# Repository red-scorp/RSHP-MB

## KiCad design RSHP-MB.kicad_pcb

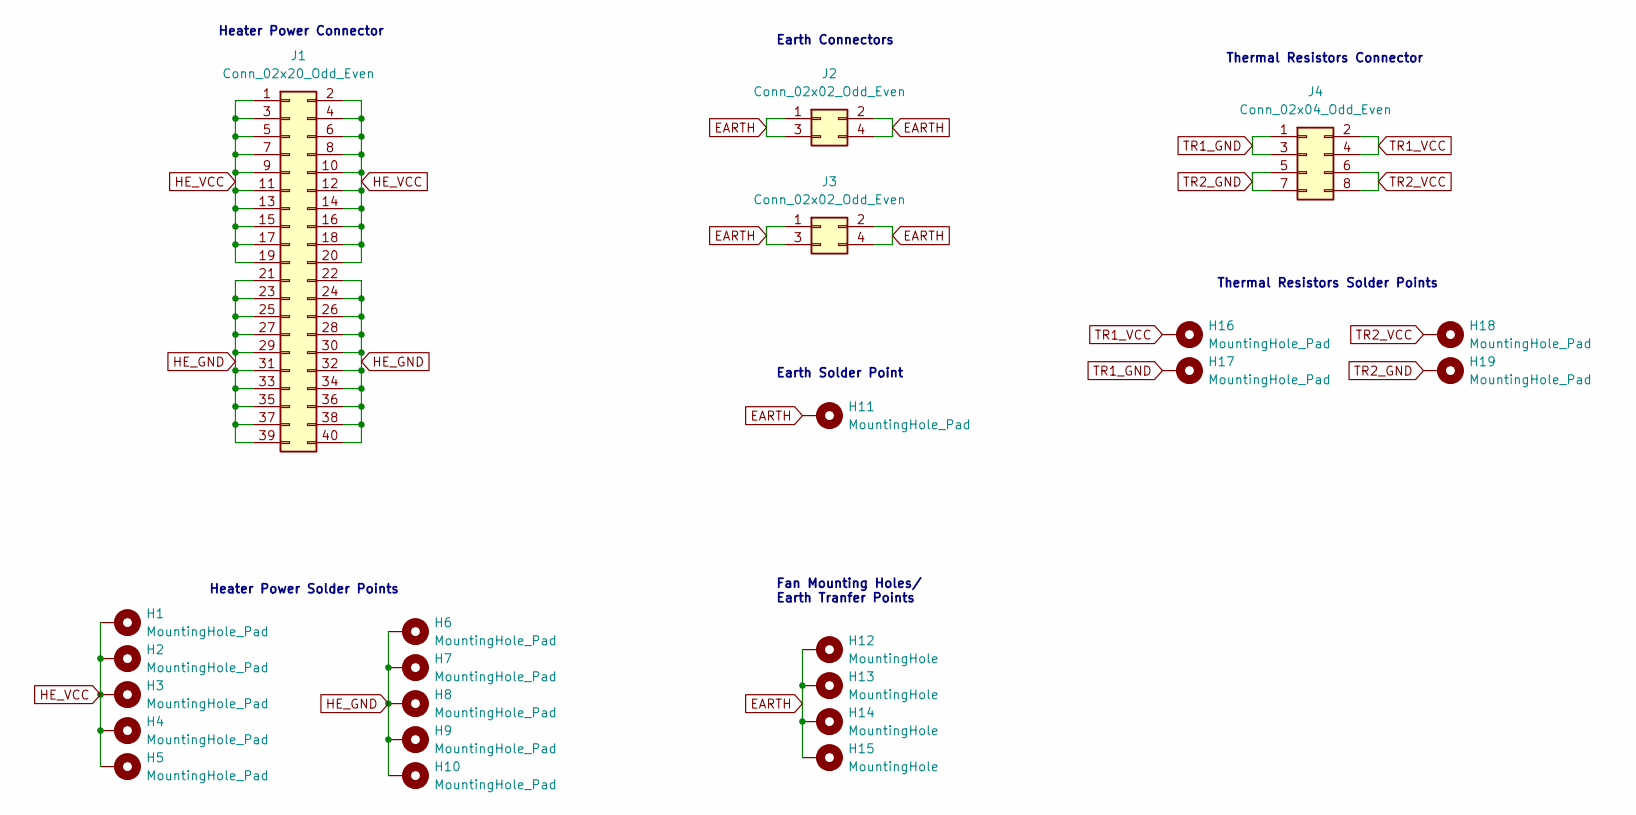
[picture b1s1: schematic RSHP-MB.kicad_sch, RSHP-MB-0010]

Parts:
H1, H2, H3, H4, H5, H6, H7, H8, H9, H10, H11, H16, H17, H18, H19: MountingHole_Pad; MountingHole_2.2mm_M2_Pad
H12, H13, H14, H15: MountingHole; MountingHole_4.3mm_M4_Pad
J1: Conn_02x20_Odd_Even; PinHeader_2x20_P2.54mm_Vertical
J2, J3: Conn_02x02_Odd_Even; PinHeader_2x02_P2.54mm_Vertical
J4: Conn_02x04_Odd_Even; PinHeader_2x04_P2.54mm_Vertical

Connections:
EARTH: H11.1, H12.1, H13.1, H14.1, H15.1, J2.1, J2.2, J2.3, J2.4, J3.1, J3.2, J3.3, J3.4
HE_GND: H6.1, H7.1, H8.1, H9.1, H10.1, J1.21, J1.22, J1.23, J1.24, J1.25, J1.26, J1.27, J1.28, J1.29, J1.30, J1.31, J1.32, J1.33, J1.34, J1.35, J1.36, J1.37, J1.38, J1.39, J1.40
HE_VCC: H1.1, H2.1, H3.1, H4.1, H5.1, J1.1, J1.2, J1.3, J1.4, J1.5, J1.6, J1.7, J1.8, J1.9, J1.10, J1.11, J1.12, J1.13, J1.14, J1.15, J1.16, J1.17, J1.18, J1.19, J1.20
TR1_GND: H17.1, J4.1, J4.3
TR1_VCC: H16.1, J4.2, J4.4
TR2_GND: H19.1, J4.5, J4.7
TR2_VCC: H18.1, J4.6, J4.8

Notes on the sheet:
Fan Mounting Holes/ Earth Tranfer Points
Heater Power Connector
Earth Connectors
Heater Power Solder Points
Earth Solder Point
Thermal Resistors Connector
Thermal Resistors Solder Points

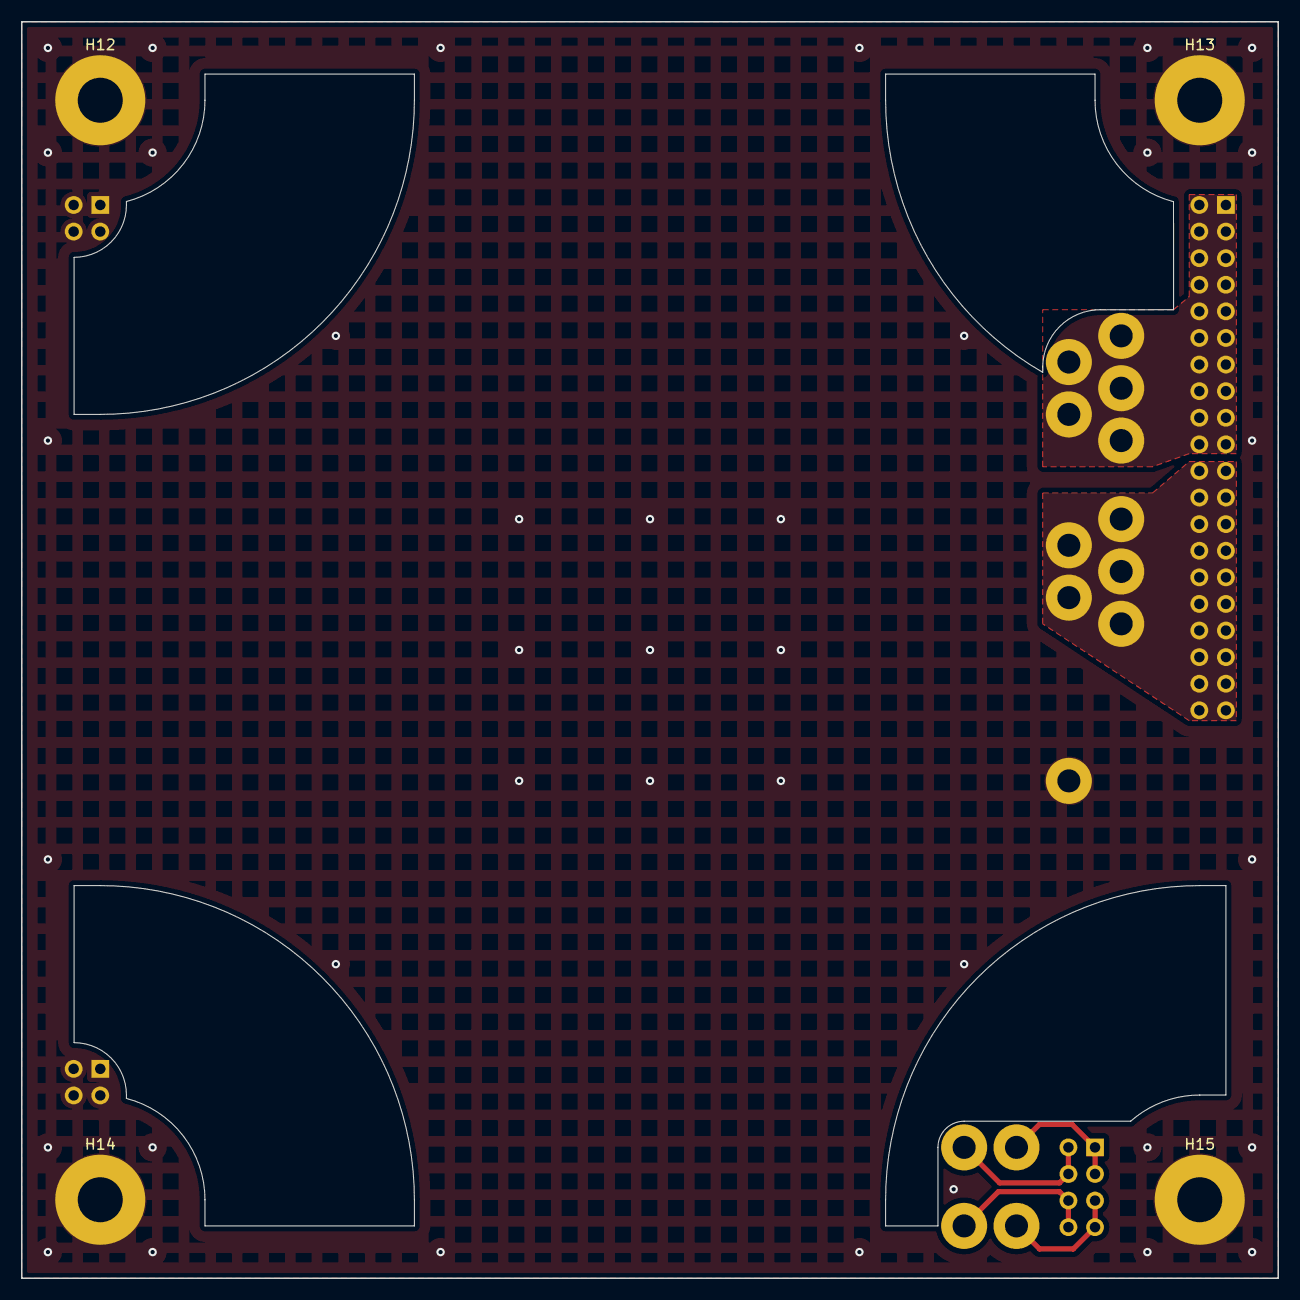
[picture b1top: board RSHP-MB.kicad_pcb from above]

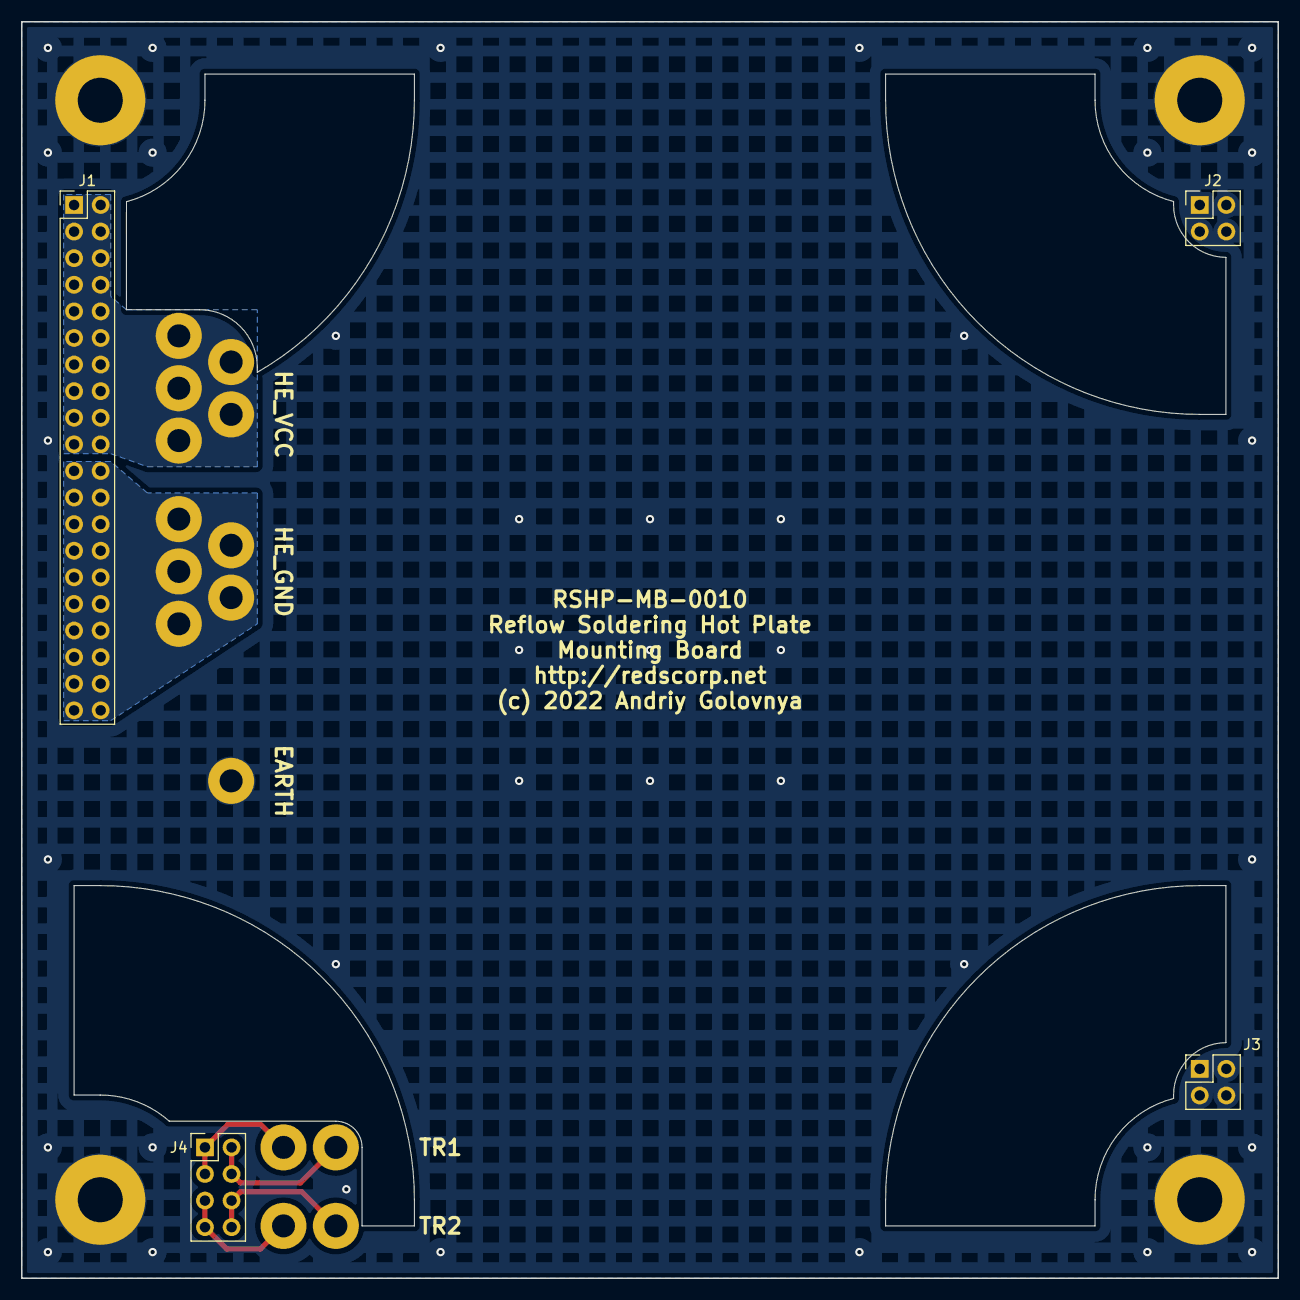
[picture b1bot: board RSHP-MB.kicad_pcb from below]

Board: 2 copper layers, 120.0 x 120.0 mm, 23 parts (4 on the bottom side), 7 nets.

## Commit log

2022-05-21 Copied schematics from RSHP-CB and changed pins order on TR socket
2022-05-21 Copied RSHP-CB PCB and changed cuts and pin headers
2022-05-21 Minor fixes after DRC check
2022-05-21 Properly filled document metadata
2022-05-22 Switched TR connector sides in schematics. rounded some corners on PCB.
2022-05-22 Put release date on today
2022-05-22 Generated CAM files
2022-05-25 Changed mount holes to M4 diameter. Generated CAM files.
2022-05-26 Generated PDF schematics. Generated PNG preview.
2022-05-29 Made TR1 and TR2 wires thicker. Generated CAM files.
2022-06-02 Added dimensions to the PCB file

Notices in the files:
RSHP-MB.kicad_pcb:
(c) 2022 Andriy Golovnya
